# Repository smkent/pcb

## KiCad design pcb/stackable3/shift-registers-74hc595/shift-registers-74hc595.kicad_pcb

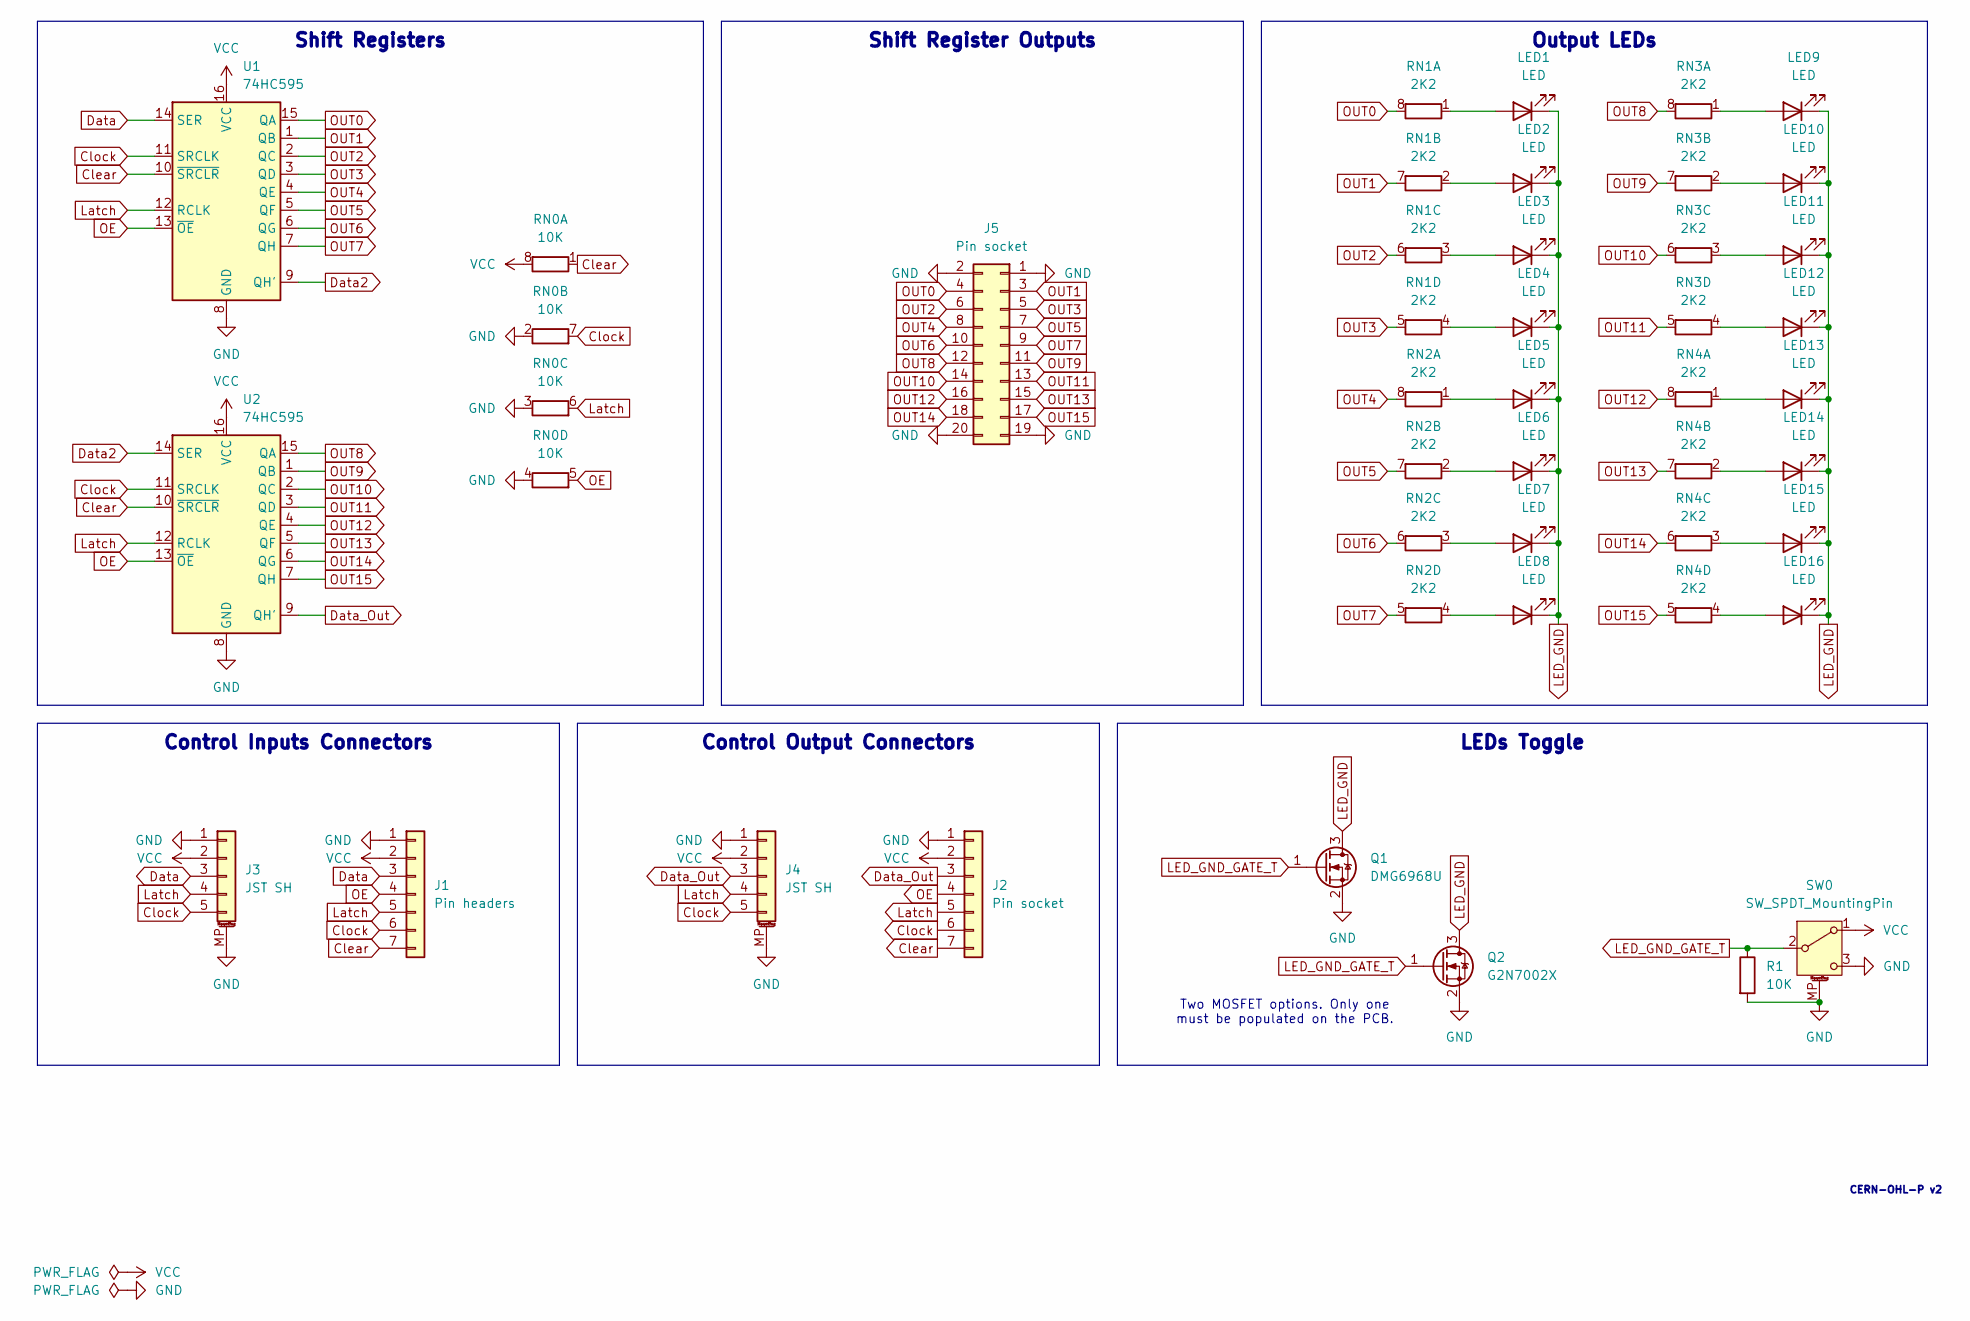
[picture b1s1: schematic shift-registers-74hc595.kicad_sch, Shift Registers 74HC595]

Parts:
J1: Pin headers; PinHeader_1x07_P2.54mm_Horizontal
J2: Pin socket; PinSocket_1x07_P2.54mm_Horizontal
J3, J4: JST SH; JST_SH_SM05B-SRSS-TB_1x05-1MP_P1.00mm_Horizontal; LCSC Part C7433426
J5: Pin socket; PinHeader_2x10_P2.54mm_Vertical
LED1, LED2, LED3, LED4, LED5, LED6, LED7, LED8, LED9, LED10, LED11, LED12, LED13, LED14, LED15, LED16: LED; LED_0603_1608Metric
Q1: DMG6968U; SOT-23; LCSC Part C150759
Q2: G2N7002X; SOT-523; LCSC Part C5258971
R1: 10K; R_0402_1005Metric
RN0: 10K; R_Array_Convex_4x0402
RN1, RN2, RN3, RN4: 2K2; R_Array_Convex_4x0603_HandSolder
SW0: SW_SPDT_MountingPin; SW_SPDT_PCM12; LCSC Part C319020
U1, U2: 74HC595; SOIC-16_3.9x9.9mm_P1.27mm

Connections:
Clear: J1.7, J2.7, RN0.1 (R1.1), U1.10 (~SRCLR), U2.10 (~SRCLR)
Clock: J1.6, J2.6, J3.5, J4.5, RN0.7 (R2.2), U1.11 (SRCLK), U2.11 (SRCLK)
Data: J1.3, J3.3, U1.14 (SER)
Data2: U1.9 (QH'), U2.14 (SER)
Data_Out: J2.3, J4.3, U2.9 (QH')
GND: J1.1, J2.1, J3.1, J3.MP (MountPin), J4.1, J4.MP (MountPin), J5.1, J5.2, J5.19, J5.20, Q1.2 (S), Q2.2 (S), R1.2, RN0.2 (R2.1), RN0.3 (R3.1), RN0.4 (R4.1), SW0.3 (C), SW0.MP (MountPin), U1.8 (GND), U2.8 (GND)
LED_GND: LED1.1 (K), LED2.1 (K), LED3.1 (K), LED4.1 (K), LED5.1 (K), LED6.1 (K), LED7.1 (K), LED8.1 (K), LED9.1 (K), LED10.1 (K), LED11.1 (K), LED12.1 (K), LED13.1 (K), LED14.1 (K), LED15.1 (K), LED16.1 (K), Q1.3 (D), Q2.3 (D)
LED_GND_GATE_T: Q1.1 (G), Q2.1 (G), R1.1, SW0.2 (B)
Latch: J1.5, J2.5, J3.4, J4.4, RN0.6 (R3.2), U1.12 (RCLK), U2.12 (RCLK)
unnamed: LED1.2 (A), RN1.1 (R1.1)
unnamed: LED2.2 (A), RN1.2 (R2.1)
unnamed: LED3.2 (A), RN1.3 (R3.1)
unnamed: LED4.2 (A), RN1.4 (R4.1)
unnamed: LED5.2 (A), RN2.1 (R1.1)
unnamed: LED6.2 (A), RN2.2 (R2.1)
unnamed: LED7.2 (A), RN2.3 (R3.1)
unnamed: LED8.2 (A), RN2.4 (R4.1)
unnamed: LED9.2 (A), RN3.1 (R1.1)
unnamed: LED10.2 (A), RN3.2 (R2.1)
unnamed: LED11.2 (A), RN3.3 (R3.1)
unnamed: LED12.2 (A), RN3.4 (R4.1)
unnamed: LED13.2 (A), RN4.1 (R1.1)
unnamed: LED14.2 (A), RN4.2 (R2.1)
unnamed: LED15.2 (A), RN4.3 (R3.1)
unnamed: LED16.2 (A), RN4.4 (R4.1)
OE: J1.4, J2.4, RN0.5 (R4.2), U1.13 (~OE), U2.13 (~OE)
OUT0: J5.4, RN1.8 (R1.2), U1.15 (QA)
OUT1: J5.3, RN1.7 (R2.2), U1.1 (QB)
OUT2: J5.6, RN1.6 (R3.2), U1.2 (QC)
OUT3: J5.5, RN1.5 (R4.2), U1.3 (QD)
OUT4: J5.8, RN2.8 (R1.2), U1.4 (QE)
OUT5: J5.7, RN2.7 (R2.2), U1.5 (QF)
OUT6: J5.10, RN2.6 (R3.2), U1.6 (QG)
OUT7: J5.9, RN2.5 (R4.2), U1.7 (QH)
OUT8: J5.12, RN3.8 (R1.2), U2.15 (QA)
OUT9: J5.11, RN3.7 (R2.2), U2.1 (QB)
OUT10: J5.14, RN3.6 (R3.2), U2.2 (QC)
OUT11: J5.13, RN3.5 (R4.2), U2.3 (QD)
OUT12: J5.16, RN4.8 (R1.2), U2.4 (QE)
OUT13: J5.15, RN4.7 (R2.2), U2.5 (QF)
OUT14: J5.18, RN4.6 (R3.2), U2.6 (QG)
OUT15: J5.17, RN4.5 (R4.2), U2.7 (QH)
VCC: J1.2, J2.2, J3.2, J4.2, RN0.8 (R1.2), SW0.1 (A), U1.16 (VCC), U2.16 (VCC)

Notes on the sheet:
Output LEDs
Control Inputs Connectors
Shift Registers
Control Output Connectors
LEDs Toggle
Shift Register Outputs
CERN-OHL-P v2
Two MOSFET options. Only one must be populated on the PCB.

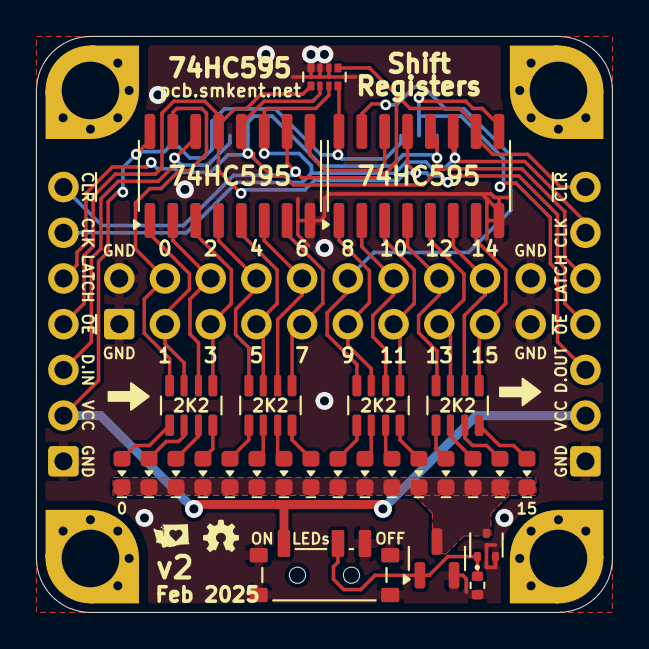
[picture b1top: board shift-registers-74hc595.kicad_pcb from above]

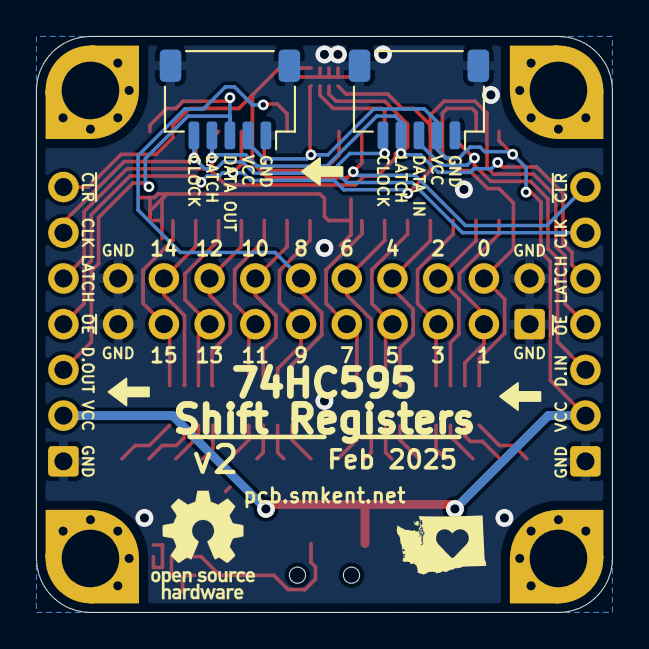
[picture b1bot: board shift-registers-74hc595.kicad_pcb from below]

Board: 2 copper layers, 32.0 x 32.0 mm, 32 parts (2 on the bottom side), 43 nets.

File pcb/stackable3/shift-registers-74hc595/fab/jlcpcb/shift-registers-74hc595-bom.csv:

Comment,Designator,Footprint,LCSC
74HC595,"U1,U2",Package_SO:SOIC-16_3.9x9.9mm_P1.27mm,
LED,"LED1,LED2,LED3,LED4,LED5,LED6,LED7,LED8,LED9,LED10,LED11,LED12,LED13,LED14,LED15,LED16",discrete:LED_0603_1608Metric,
JST SH,"J3,J4",connector:JST_SH_SM05B-SRSS-TB_1x05-1MP_P1.00mm_Horizontal,C7433426
2K2,"RN1,RN2,RN3,RN4",discrete:R_Array_Convex_4x0603_HandSolder,
10K,RN0,discrete:R_Array_Convex_4x0402,C110924
Pin headers,J1,connector:PinHeader_1x07_P2.54mm_Horizontal,
10K,R1,Resistor_SMD:R_0402_1005Metric,
DMG6968U,Q1,Package_TO_SOT_SMD:SOT-23,C150759
Pin socket,J2,connector:PinSocket_1x07_P2.54mm_Horizontal,
SW_SPDT_MountingPin,SW0,electromechanical:SW_SPDT_PCM12,C319020
Pin socket,J5,connector:PinHeader_2x10_P2.54mm_Vertical,
G2N7002X,Q2,package:SOT-523,C5258971

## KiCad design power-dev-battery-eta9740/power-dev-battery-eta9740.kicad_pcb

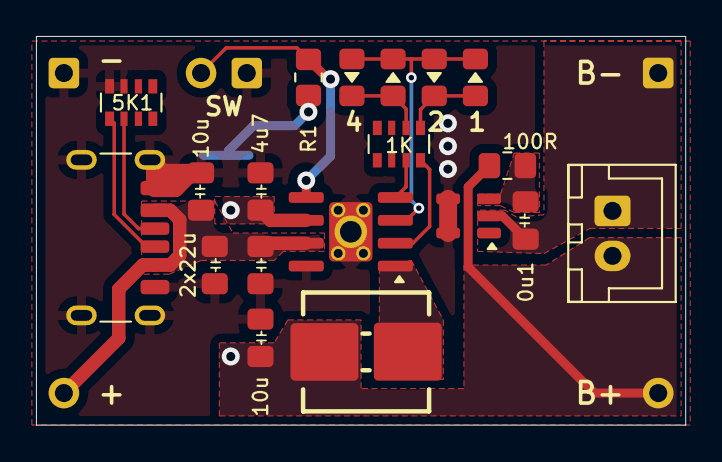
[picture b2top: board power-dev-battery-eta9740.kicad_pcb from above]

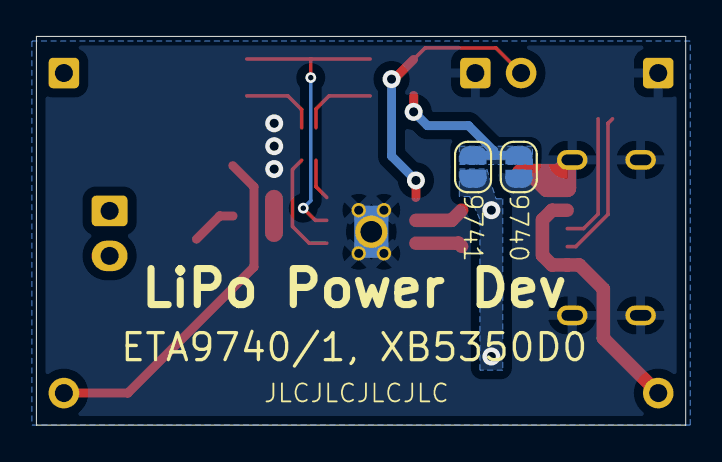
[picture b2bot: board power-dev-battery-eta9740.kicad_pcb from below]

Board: 2 copper layers, 36.1 x 21.6 mm, 26 parts (2 on the bottom side), 15 nets.

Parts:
BT1: Battery_Cell; JST_XH_B2B-XH-A_1x02_P2.50mm_Vertical_simple_pad2gnd
C1: 0.1uF; C_0805_2012Metric_Pad1.18x1.45mm_HandSolder
Cbat1: 4.7uF; C_0805_2012Metric_Pad1.18x1.45mm_HandSolder
Cin1: 10uF; C_0805_2012Metric_Pad1.18x1.45mm_HandSolder
Cout1, Cout2: 22uF; C_0805_2012Metric_Pad1.18x1.45mm_HandSolder
Cusb1: 10uF; C_0805_2012Metric_Pad1.18x1.45mm_HandSolder
J0: USB_C_Receptacle_PowerOnly_6P; USB_C_Receptacle_GCT_USB4125-xx-x_6P_TopMnt_Horizontal_hand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
J1, J3: Conn_01x01; PinHeader_1x01_P2.54mm_simple
J2, J4: Conn_01x01; PinHeader_1x01_P2.54mm_simple_square
JP1, JP2: SolderJumper_2_Open; SolderJumper-2_P1.3mm_Open_RoundedPad1.0x1.5mm
L1: 22uH; Inductor_Multi_7.0x6.6_plus
LED1, LED2, LED3, LED4: LED_0805_2012Metric_Pad1.15x1.40mm_HandSolder_simple
R1: 100K; R_0805_2012Metric_Pad1.20x1.40mm_HandSolder
R2: 100R; R_0805_2012Metric_Pad1.20x1.40mm_HandSolder
RN1: R_Pack04_Split; R_Array_Convex_4x0603
RN2: 5K1; R_Array_Convex_4x0603
SW1: SW_Push; PinHeader_1x02_P2.54mm_Vertical_simple_pad2gnd
U1: ETA9740E8A; SOIC-8-1EP_3.9x4.9mm_P1.27mm_EP2.41x3.3mm_ThermalVias_Custo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
U2: XB5350D0; SOT-23-5_simple

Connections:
0/1_SEL: JP1.2 (B), JP2.1 (A), R1.1
AGND: Cbat1.1, Cin1.1, Cout1.2, Cout2.2, Cusb1.2, J0.A12 (GND), J0.B12 (GND), J0.S1 (SHIELD), J2.1, JP1.1 (A), RN2.7 (R2.2), RN2.8 (R1.2), SW1.2, U1.8 (PGND), U1.9 (AGND), U2.4 (VM), U2.5 (VM)
B+: BT1.1 (+), Cbat1.2, Cin1.2, J3.1, JP2.2 (B), L1.1, R2.1, U1.6 (BAT)
B-: BT1.2 (-), C1.1, J4.1, U2.2 (GND)
BATVDD: C1.2, R2.2, U2.3 (VDD)
ISET: R1.2, SW1.1, U1.5 (ISET)
LED1: RN1.4 (R4.1), U1.2 (LED1)
LED2: LED1.1 (K), LED2.2 (A), LED3.1 (K), LED4.2 (A), U1.3 (LED2)
LED3: RN1.3 (R3.1), U1.4 (LED3)
unnamed: J0.A5 (CC1), RN2.2 (R2.1)
unnamed: J0.B5 (CC2), RN2.1 (R1.1)
unnamed: LED1.2 (A), LED2.1 (K), RN1.5 (R4.2)
unnamed: LED3.2 (A), LED4.1 (K), RN1.6 (R3.2)
SW: L1.2, U1.1 (SW)
VCC: Cout1.1, Cout2.1, Cusb1.1, J0.A9 (VBUS), J0.B9 (VBUS), J1.1, U1.7 (OUT)

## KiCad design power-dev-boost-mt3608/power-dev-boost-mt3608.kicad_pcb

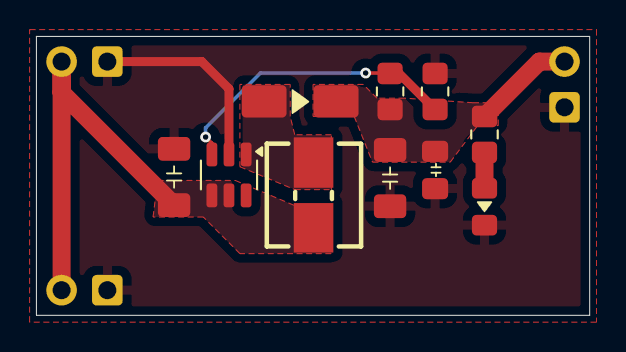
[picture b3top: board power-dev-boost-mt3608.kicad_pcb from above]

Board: 2 copper layers, 30.7 x 15.5 mm, 13 parts (0 on the bottom side), 6 nets.

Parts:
C1: 22uF; C_1206_3216Metric_Pad1.33x1.80mm_HandSolder
C2: 22uf; C_1206_3216Metric_Pad1.33x1.80mm_HandSolder
C3: 10uF; C_0805_2012Metric_Pad1.18x1.45mm_HandSolder
D1: SS34; D_SMA_simple
J1, J2, J3: Conn_01x02; PinHeader_1x02_P2.54mm_Vertical_simple_pad2gnd
L1: 22uH; Inductor_Multi_5.2x5.7_2x2.5
LED1: Boost; LED_0805_2012Metric_Pad1.15x1.40mm_HandSolder_simple
R1: 75K; R_0805_2012Metric_Pad1.20x1.40mm_HandSolder
R2, R3: 10K; R_0805_2012Metric_Pad1.20x1.40mm_HandSolder
U1: MT3608; SOT-23-6

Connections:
FB: R1.2, R2.1, U1.3 (FB)
GND: C1.2, C2.2, C3.2, J1.2, J2.2, J3.2, LED1.1 (K), R2.2, U1.2 (GND)
unnamed: LED1.2 (A), R3.2
SW: D1.2 (A), L1.2, U1.1 (SW)
VCC: C1.1, J1.1, J2.1, L1.1, U1.4 (EN), U1.5 (IN)
VOUT: C2.1, C3.1, D1.1 (K), J3.1, R1.1, R3.1

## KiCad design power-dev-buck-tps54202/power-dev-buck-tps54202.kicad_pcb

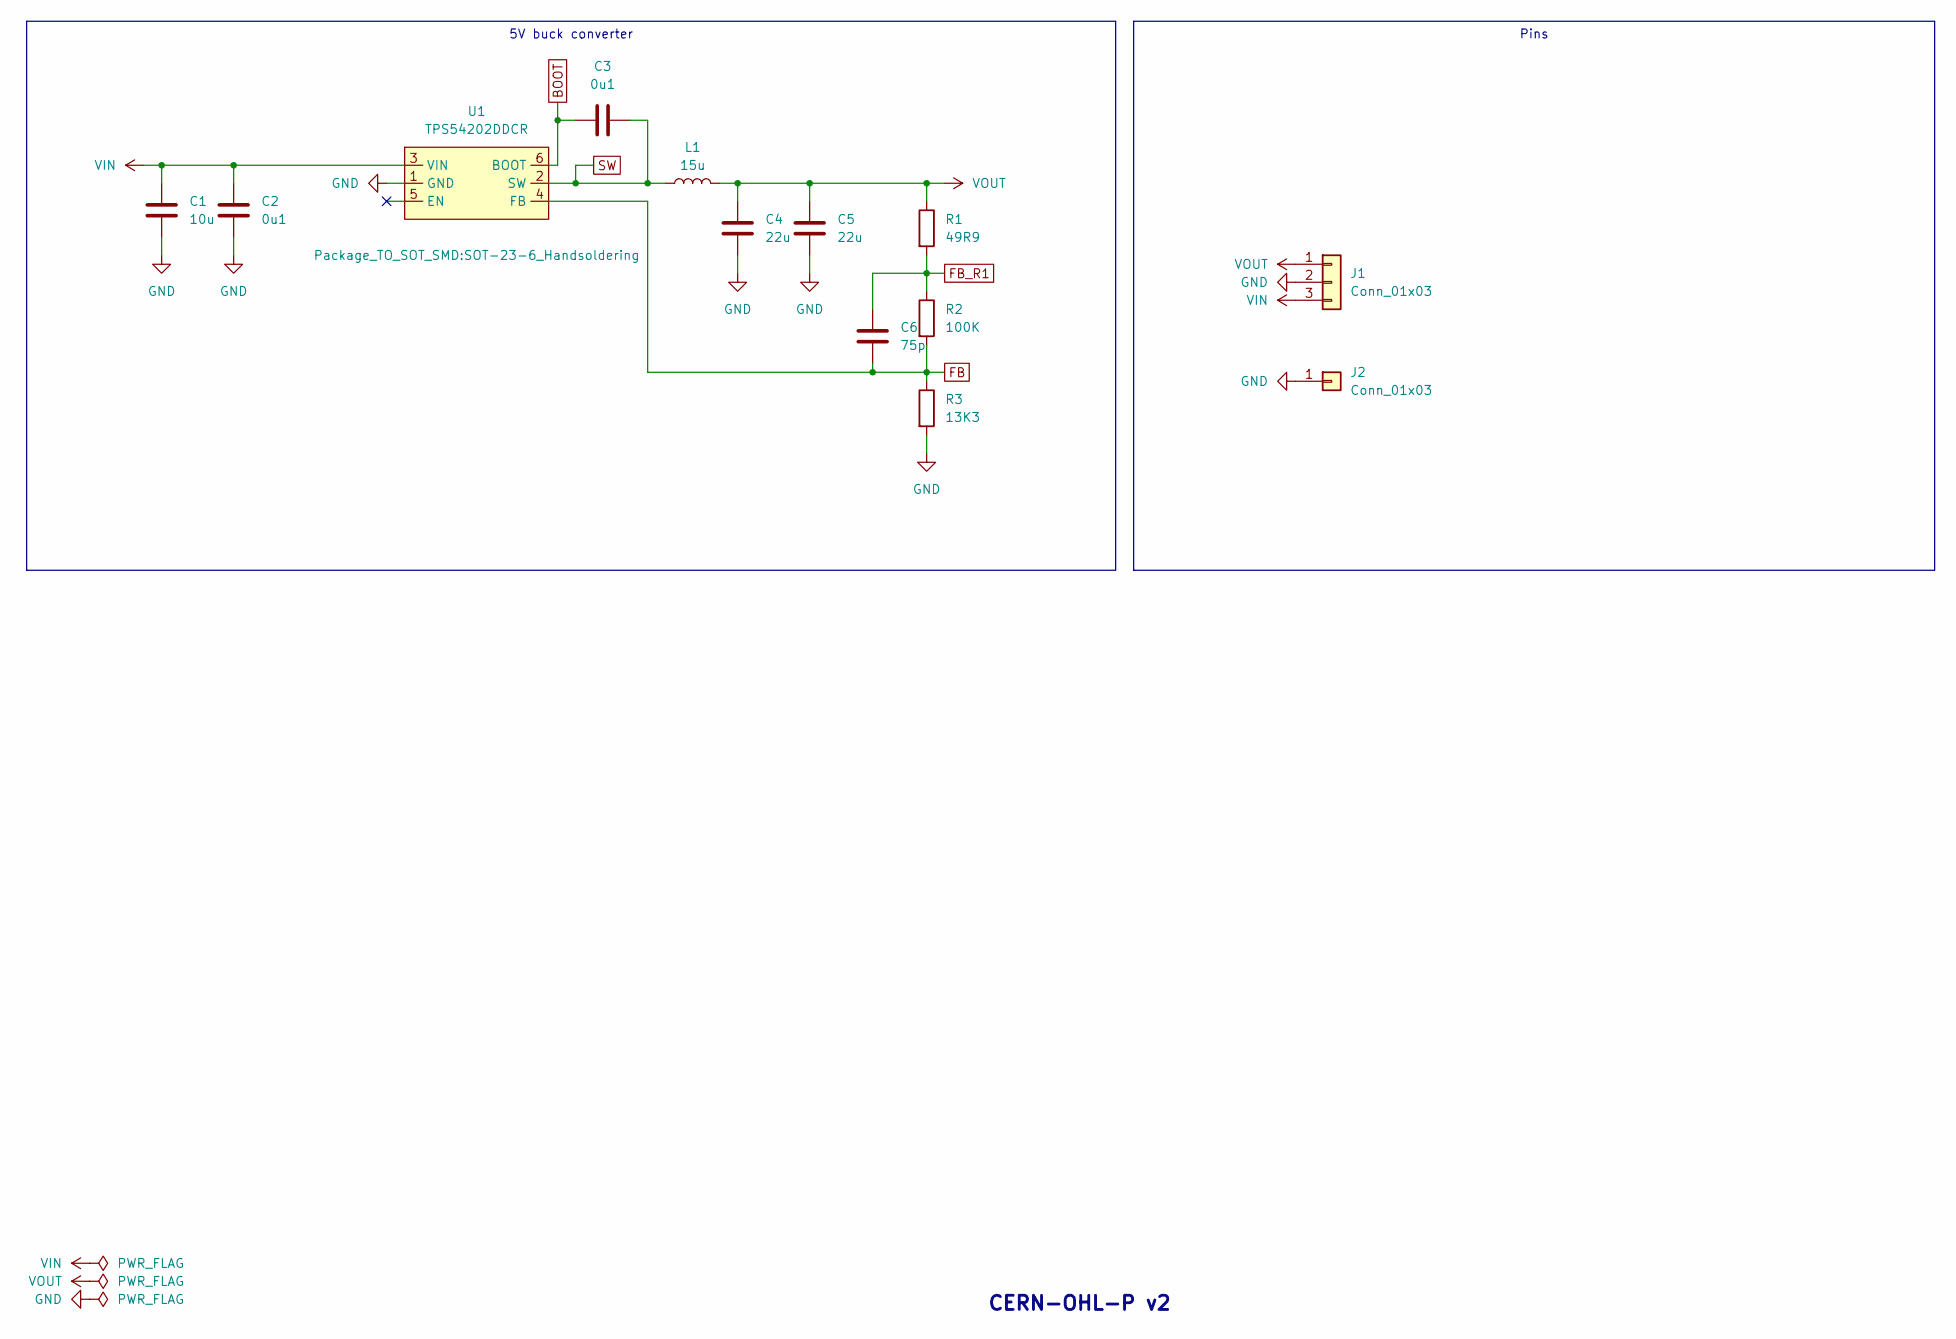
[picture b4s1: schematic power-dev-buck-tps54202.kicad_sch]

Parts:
C1: 10u; C_0805_2012Metric_Pad1.18x1.45mm_HandSolder
C2, C3: 0u1; C_0805_2012Metric_Pad1.18x1.45mm_HandSolder
C4, C5: 22u; C_0805_2012Metric_Pad1.18x1.45mm_HandSolder
C6: 75p; C_0805_2012Metric_Pad1.18x1.45mm_HandSolder
J1: Conn_01x03; PinHeader_1x03_P2.54mm_Vertical_simple_pad2gnd
J2: Conn_01x03; PinHeader_1x01_P2.54mm_simple_square
L1: 15u; Inductor_Multi_5.2x5.7_2x2.5
R1: 49R9; R_0805_2012Metric_Pad1.20x1.40mm_HandSolder
R2: 100K; R_0805_2012Metric_Pad1.20x1.40mm_HandSolder
R3: 13K3; R_0805_2012Metric_Pad1.20x1.40mm_HandSolder
U1: TPS54202DDCR; SOT-23-6_Handsoldering; LCSC Part C191884

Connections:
BOOT: C3.1, U1.6 (BOOT)
FB: C6.2, R2.2, R3.1, U1.4 (FB)
FB_R1: C6.1, R1.2, R2.1
GND: C1.2, C2.2, C4.2, C5.2, J1.2, J2.1, R3.2, U1.1 (GND)
SW: C3.2, L1.1, U1.2 (SW)
VIN: C1.1, C2.1, J1.3, U1.3 (VIN)
VOUT: C4.1, C5.1, J1.1, L1.2, R1.1

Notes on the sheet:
5V buck converter
Pins
CERN-OHL-P v2

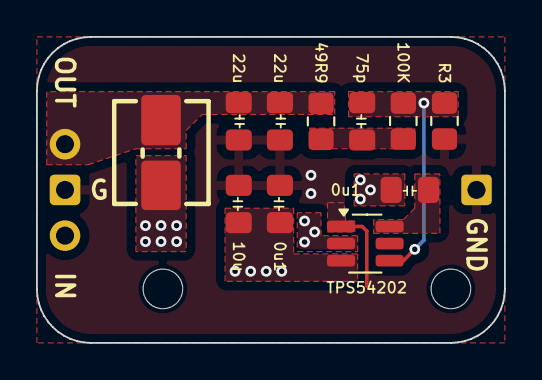
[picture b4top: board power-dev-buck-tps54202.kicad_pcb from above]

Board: 2 copper layers, 26.0 x 17.0 mm, 13 parts (0 on the bottom side), 7 nets.

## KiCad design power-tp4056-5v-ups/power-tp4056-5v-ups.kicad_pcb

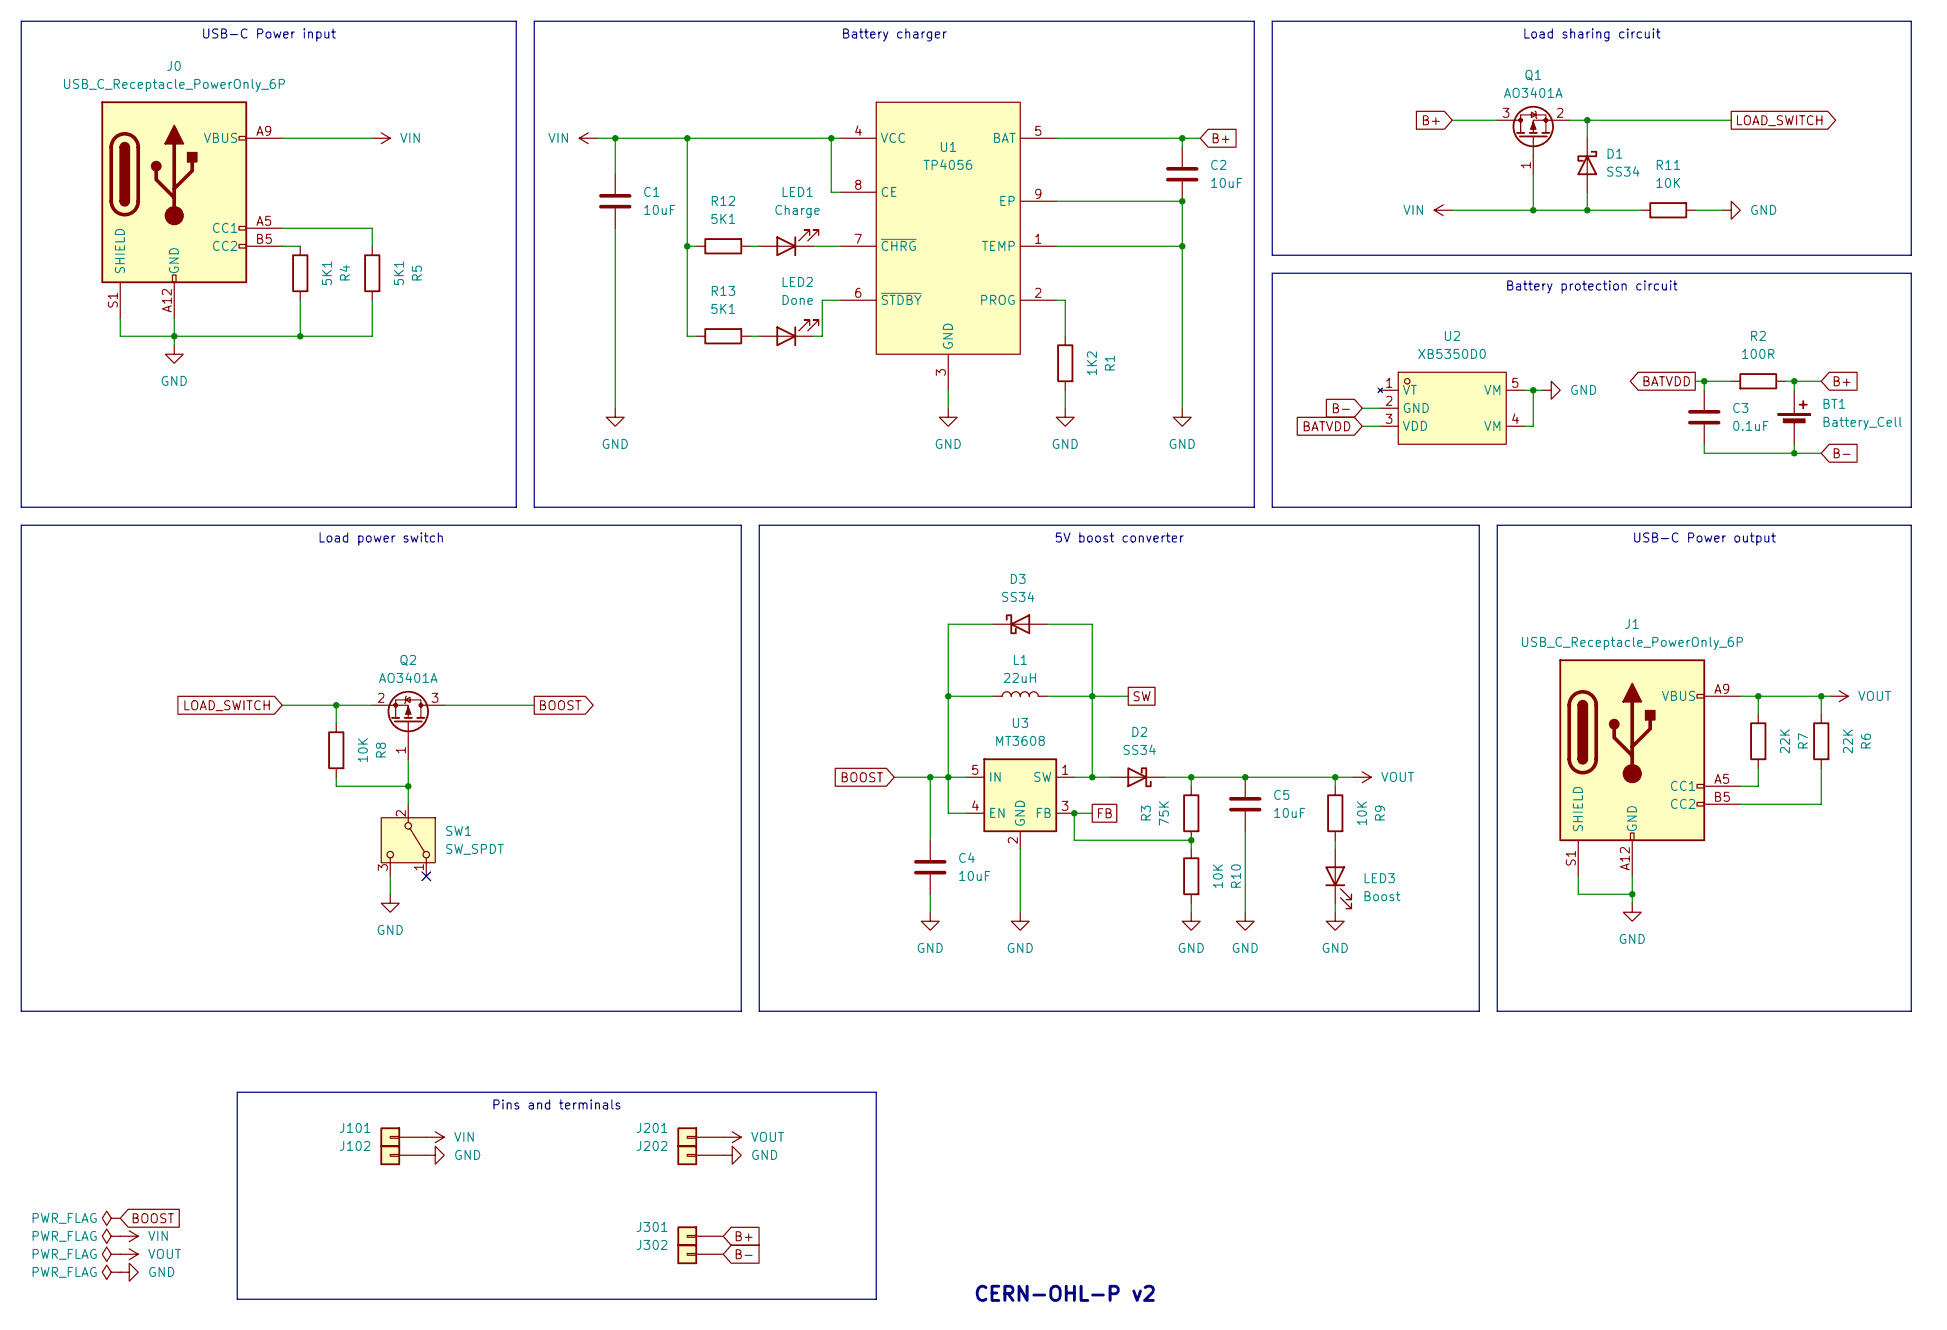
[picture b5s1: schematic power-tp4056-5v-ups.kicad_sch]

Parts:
BT1: Battery_Cell; JST_XH_B2B-XH-A_1x02_P2.50mm_Vertical_simple_pad2gnd
C1, C2, C4: 10uF; C_0603_1608Metric; LCSC Part C19702
C3: 0.1uF; C_0402_1005Metric; LCSC Part C1525
C5: 10uF; C_0402_1005Metric; LCSC Part C15525
D1, D2, D3: SS34; D_SMA_simple; LCSC Part C8678
J0, J1: USB_C_Receptacle_PowerOnly_6P; USB_C_Receptacle_GCT_USB4125-xx-x_6P_TopMnt_Horizontal_hand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
J101, J201, J301: Conn_01x01; PinHeader_1x01_P2.54mm_simple
J102, J202, J302: Conn_01x01; PinHeader_1x01_P2.54mm_simple_square
L1: 22uH; IND-SMD_L7.0-W6.6; LCSC Part C5832376
LED1: Charge; LED_0805_2012Metric_Pad1.15x1.40mm_HandSolder_simple
LED2: Done; LED_0805_2012Metric_Pad1.15x1.40mm_HandSolder_simple
LED3: Boost; LED_0805_2012Metric_Pad1.15x1.40mm_HandSolder_simple
Q1, Q2: AO3401A; SOT-23; LCSC Part C15127
R1: 1K2; R_0805_2012Metric_Pad1.20x1.40mm_HandSolder; LCSC Part C17379
R2: 100R; R_0805_2012Metric_Pad1.20x1.40mm_HandSolder; LCSC Part C17408
R3: 75K; R_0402_1005Metric; LCSC Part C25798
R4, R5, R12, R13: 5K1; R_0402_1005Metric; LCSC Part C25905
R6, R7: 22K; R_0402_1005Metric; LCSC Part C25768
R8, R9, R10, R11: 10K; R_0402_1005Metric; LCSC Part C25744
SW1: SW_SPDT; SW-TH_DEALON_SS-12D01-GX_simple; LCSC Part C2998803
U1: TP4056; SOIC-8-1EP_3.9x4.9mm_P1.27mm_EP2.41x3.3mm_ThermalVias_Custo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; JLCPCB_CORRECTION 0; 0; 270
U2: XB5350D0; SOT-23-5_simple; JLCPCB_CORRECTION 0; 0; 180
U3: MT3608; SOT-23-6; LCSC Part C84817

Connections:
B+: BT1.1 (+), C2.2, J301.1, Q1.3 (D), R2.1, U1.5 (BAT)
B-: BT1.2 (-), C3.1, J302.1, U2.2 (GND)
BATVDD: C3.2, R2.2, U2.3 (VDD)
BOOST: C4.1, D3.1 (K), L1.1, Q2.3 (D), U3.4 (EN), U3.5 (IN)
FB: R3.2, R10.1, U3.3 (FB)
GND: C1.2, C2.1, C4.2, C5.2, J0.A12 (GND), J0.B12 (GND), J0.S1 (SHIELD), J1.A12 (GND), J1.B12 (GND), J1.S1 (SHIELD), J102.1, J202.1, LED3.1 (K), R1.2, R4.2, R5.2, R10.2, R11.2, SW1.3 (C), U1.1 (TEMP), U1.3 (GND), U1.9 (EP), U2.4 (VM), U2.5 (VM), U3.2 (GND)
LOAD_SWITCH: D1.1 (K), Q1.2 (S), Q2.2 (S), R8.1
unnamed: J0.A5 (CC1), R5.1
unnamed: J0.B5 (CC2), R4.1
unnamed: J1.A5 (CC1), R7.2
unnamed: J1.B5 (CC2), R6.2
unnamed: LED1.2 (A), R12.2
unnamed: LED1.1 (K), U1.7 (~CHRG)
unnamed: LED2.2 (A), R13.2
unnamed: LED2.1 (K), U1.6 (~STDBY)
unnamed: LED3.2 (A), R9.2
unnamed: Q2.1 (G), R8.2, SW1.2 (B)
unnamed: R1.1, U1.2 (PROG)
SW: D2.2 (A), D3.2 (A), L1.2, U3.1 (SW)
VIN: C1.1, D1.2 (A), J0.A9 (VBUS), J0.B9 (VBUS), J101.1, Q1.1 (G), R11.1, R12.1, R13.1, U1.4 (VCC), U1.8 (CE)
VOUT: C5.1, D2.1 (K), J1.A9 (VBUS), J1.B9 (VBUS), J201.1, R3.1, R6.1, R7.1, R9.1

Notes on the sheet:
Pins and terminals
Battery protection circuit
USB-C Power output
USB-C Power input
Load sharing circuit
Load power switch
Battery charger
5V boost converter
CERN-OHL-P v2

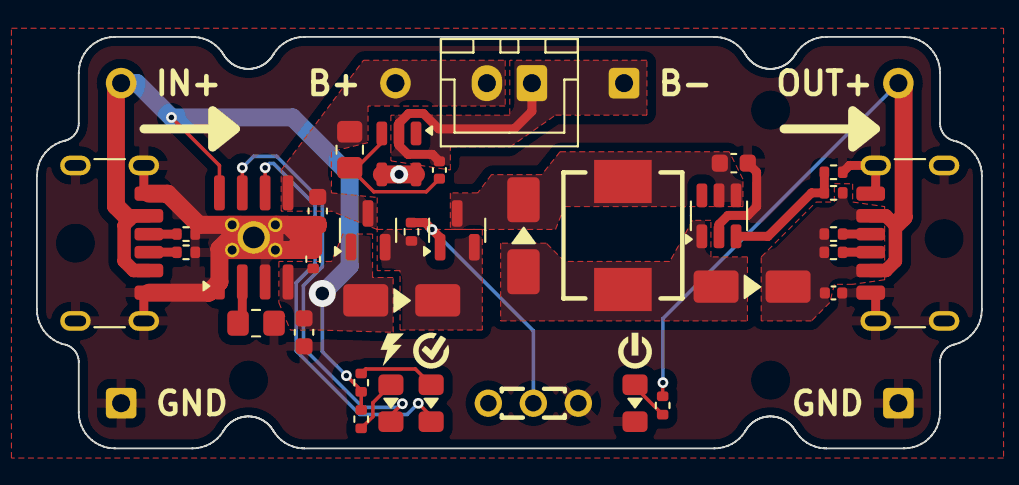
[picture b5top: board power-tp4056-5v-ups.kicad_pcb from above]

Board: 2 copper layers, 52.5 x 22.9 mm, 40 parts (0 on the bottom side), 21 nets.

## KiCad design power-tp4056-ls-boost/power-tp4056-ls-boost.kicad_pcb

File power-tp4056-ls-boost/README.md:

# Li-ion 5V UPS

Features:

* 1A Li-Ion battery charger ([TP4056][tp4056])
* Battery protection with 3V discharge cutoff ([XB5350D0][xb5350d0],
  [english translation](/datasheets/XySemi-XB5307H-en.pdf))
* Load-sharing circuit
* 5V boost converter ([MT3608][mt3608])

## Acknowledgements

Built from scratch using the IC datasheet application circuits, but inspired by
[@wagiminator][wagiminator-power-boards]'s [TP4056 LiPo Charger LS][wagiminator-tp4056-lipo-charger-ls] and
[MT3608 12V Boost Converter Stick][wagiminator-mt3608-12v-boost-converter].

[mt3608]: https://www.olimex.com/Products/Breadboarding/BB-PWR-3608/resources/MT3608.pdf
[tp4056]: https://dlnmh9ip6v2uc.cloudfront.net/datasheets/Prototyping/TP4056.pdf
[wagiminator-mt3608-12v-boost-converter]: https://github.com/wagiminator/Power-Boards/tree/master/Boost_Converter_MT3608
[wagiminator-power-boards]: https://github.com/wagiminator/Power-Boards
[wagiminator-tp4056-lipo-charger-ls]: https://github.com/wagiminator/Power-Boards/tree/master/LiPo_Charger_LS_TP4056
[xb5350d0]: https://www.lcsc.com/datasheet/lcsc_datasheet_2106062205_XySemi-XB5350D0_C2760002.pdf

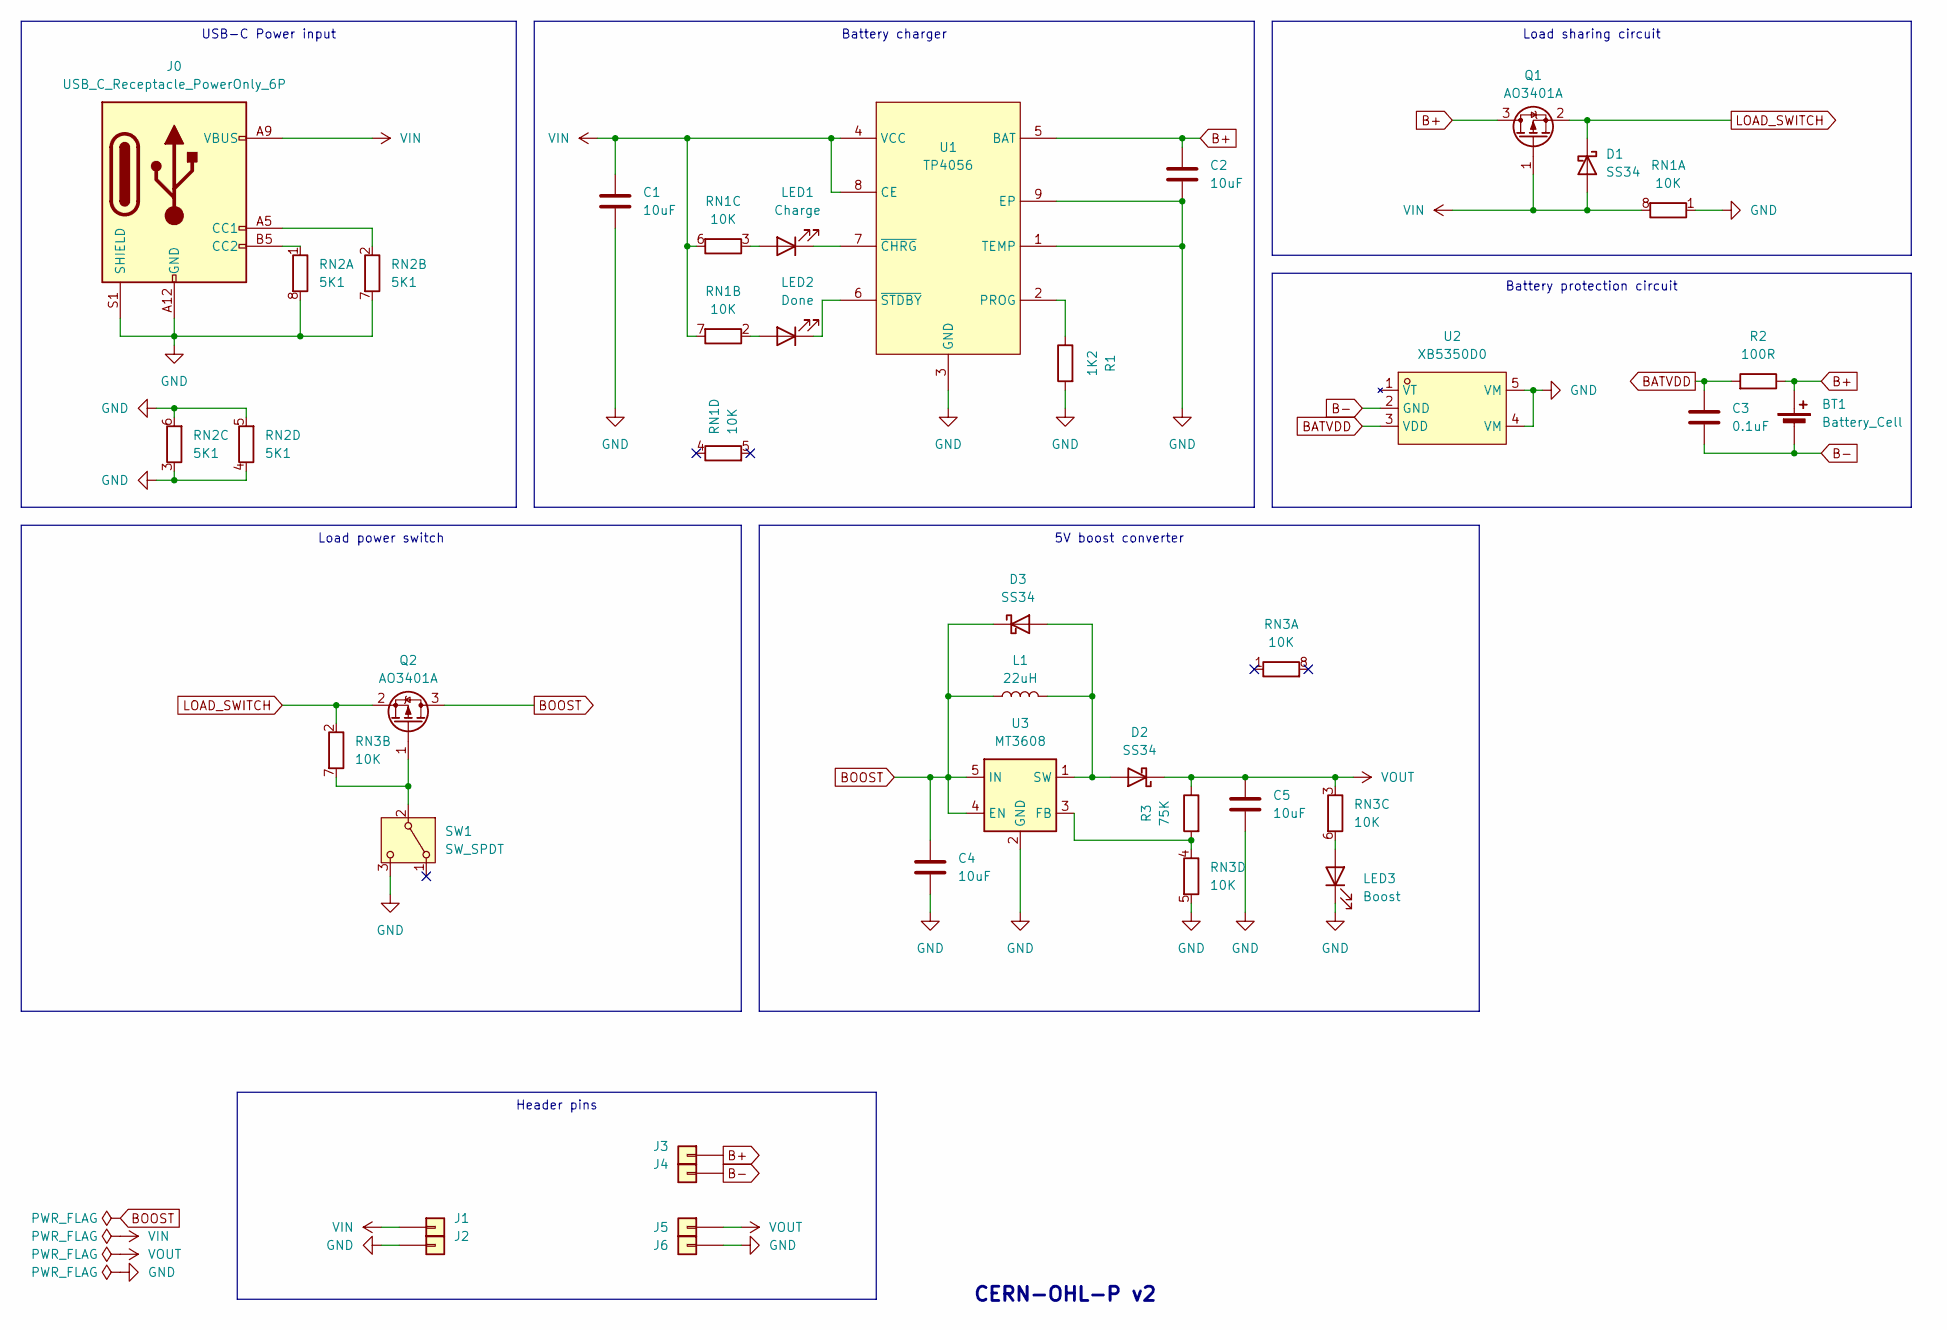
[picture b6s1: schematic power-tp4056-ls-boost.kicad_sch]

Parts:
BT1: Battery_Cell; JST_XH_B2B-XH-A_1x02_P2.50mm_Vertical_simple
C1, C2, C4, C5: 10uF; C_0805_2012Metric_Pad1.18x1.45mm_HandSolder; LCSC Part C15850
C3: 0.1uF; C_0805_2012Metric_Pad1.18x1.45mm_HandSolder; LCSC Part C28233
D1, D2, D3: SS34; D_SMA_simple; LCSC Part C8678
J0: USB_C_Receptacle_PowerOnly_6P; USB_C_Receptacle_GCT_USB4125-xx-x_6P_TopMnt_Horizontal_hand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
J1, J3, J5: Conn_01x01; PinHeader_1x01_P2.54mm_simple
J2, J4, J6: Conn_01x01; PinHeader_1x01_P2.54mm_simple_square
L1: 22uH; IND-SMD_L7.0-W6.6; LCSC Part C5832376
LED1: Charge; LED_0805_2012Metric_Pad1.15x1.40mm_HandSolder_simple
LED2: Done; LED_0805_2012Metric_Pad1.15x1.40mm_HandSolder_simple
LED3: Boost; LED_0805_2012Metric_Pad1.15x1.40mm_HandSolder_simple
Q1, Q2: AO3401A; SOT-23; LCSC Part C15127
R1: 1K2; R_0805_2012Metric_Pad1.20x1.40mm_HandSolder; LCSC Part C17379
R2: 100R; R_0805_2012Metric_Pad1.20x1.40mm_HandSolder; LCSC Part C17408
R3: 75K; R_0805_2012Metric_Pad1.20x1.40mm_HandSolder
RN1, RN3: 10K; R_Array_Convex_4x0603; LCSC Part C29718
RN2: 5K1; R_Array_Convex_4x0603
SW1: SW_SPDT; SW-TH_DEALON_SS-12D01-GX_simple; LCSC Part C2998803
U1: TP4056; SOIC-8-1EP_3.9x4.9mm_P1.27mm_EP2.41x3.3mm_ThermalVias_Custo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; JLCPCB_CORRECTION 0; 0; 270
U2: XB5350D0; SOT-23-5_simple; JLCPCB_CORRECTION 0; 0; 270
U3: MT3608; SOT-23-6; LCSC Part C84817

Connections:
B+: BT1.1 (+), C2.2, J3.1, Q1.3 (D), R2.1, U1.5 (BAT)
B-: BT1.2 (-), C3.1, J4.1, U2.2 (GND)
BATVDD: C3.2, R2.2, U2.3 (VDD)
BOOST: C4.1, D3.1 (K), L1.1, Q2.3 (D), U3.4 (EN), U3.5 (IN)
GND: C1.2, C2.1, C4.2, C5.2, J0.A12 (GND), J0.B12 (GND), J0.S1 (SHIELD), J2.1, J6.1, LED3.1 (K), R1.2, RN1.1 (R1.1), RN2.3 (R3.1), RN2.4 (R4.1), RN2.5 (R4.2), RN2.6 (R3.2), RN2.7 (R2.2), RN2.8 (R1.2), RN3.5 (R4.2), SW1.3 (C), U1.1 (TEMP), U1.3 (GND), U1.9 (EP), U2.4 (VM), U2.5 (VM), U3.2 (GND)
LOAD_SWITCH: D1.1 (K), Q1.2 (S), Q2.2 (S), RN3.2 (R2.1)
unnamed: D2.2 (A), D3.2 (A), L1.2, U3.1 (SW)
unnamed: J0.A5 (CC1), RN2.2 (R2.1)
unnamed: J0.B5 (CC2), RN2.1 (R1.1)
unnamed: LED1.2 (A), RN1.3 (R3.1)
unnamed: LED1.1 (K), U1.7 (~CHRG)
unnamed: LED2.2 (A), RN1.2 (R2.1)
unnamed: LED2.1 (K), U1.6 (~STDBY)
unnamed: LED3.2 (A), RN3.6 (R3.2)
unnamed: Q2.1 (G), RN3.7 (R2.2), SW1.2 (B)
unnamed: R3.2, RN3.4 (R4.1), U3.3 (FB)
unnamed: R1.1, U1.2 (PROG)
VIN: C1.1, D1.2 (A), J0.A9 (VBUS), J0.B9 (VBUS), J1.1, Q1.1 (G), RN1.6 (R3.2), RN1.7 (R2.2), RN1.8 (R1.2), U1.4 (VCC), U1.8 (CE)
VOUT: C5.1, D2.1 (K), J5.1, R3.1, RN3.3 (R3.1)

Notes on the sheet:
Header pins
Battery protection circuit
USB-C Power input
Load sharing circuit
Load power switch
Battery charger
5V boost converter
CERN-OHL-P v2

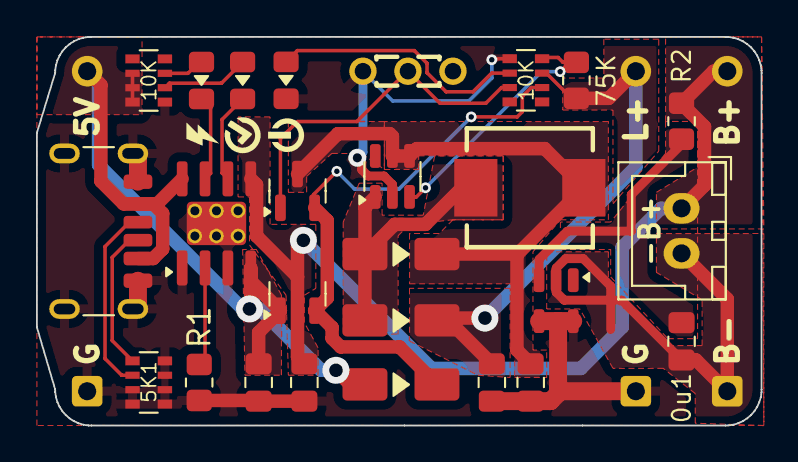
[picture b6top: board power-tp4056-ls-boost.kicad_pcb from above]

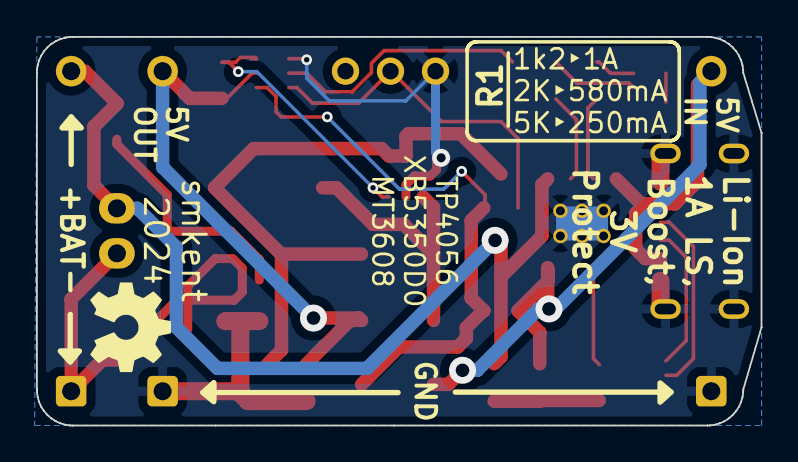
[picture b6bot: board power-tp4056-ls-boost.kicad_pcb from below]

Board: 2 copper layers, 40.3 x 21.6 mm, 32 parts (6 on the bottom side), 19 nets.
